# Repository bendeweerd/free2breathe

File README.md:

# free<sub>2</sub>breathe
Calvin University Senior Design Team 17, 2022-2023.

Free<sub>2</sub>breathe is a hazardous gas detector built using [SPEC sensors](https://www.spec-sensors.com/) and a custom PCB. It detects short-term and long-term hazardous levels of
1. Carbon Monoxide
2. Ozone
3. Sulfur Dioxide
4. Nitrogen Dioxide

and alerts the user if any of these gases are present in concentrations that will cause long-term or short-term harm.

Visit our [webpage](https://bendeweerd.github.io/free2breathe/index.html) to download the instructional pamphlet.

Team Members: 
1. Nate Anderson
2. Jordan Alexander
3. Ben DeWeerd
4. Anna Giboney

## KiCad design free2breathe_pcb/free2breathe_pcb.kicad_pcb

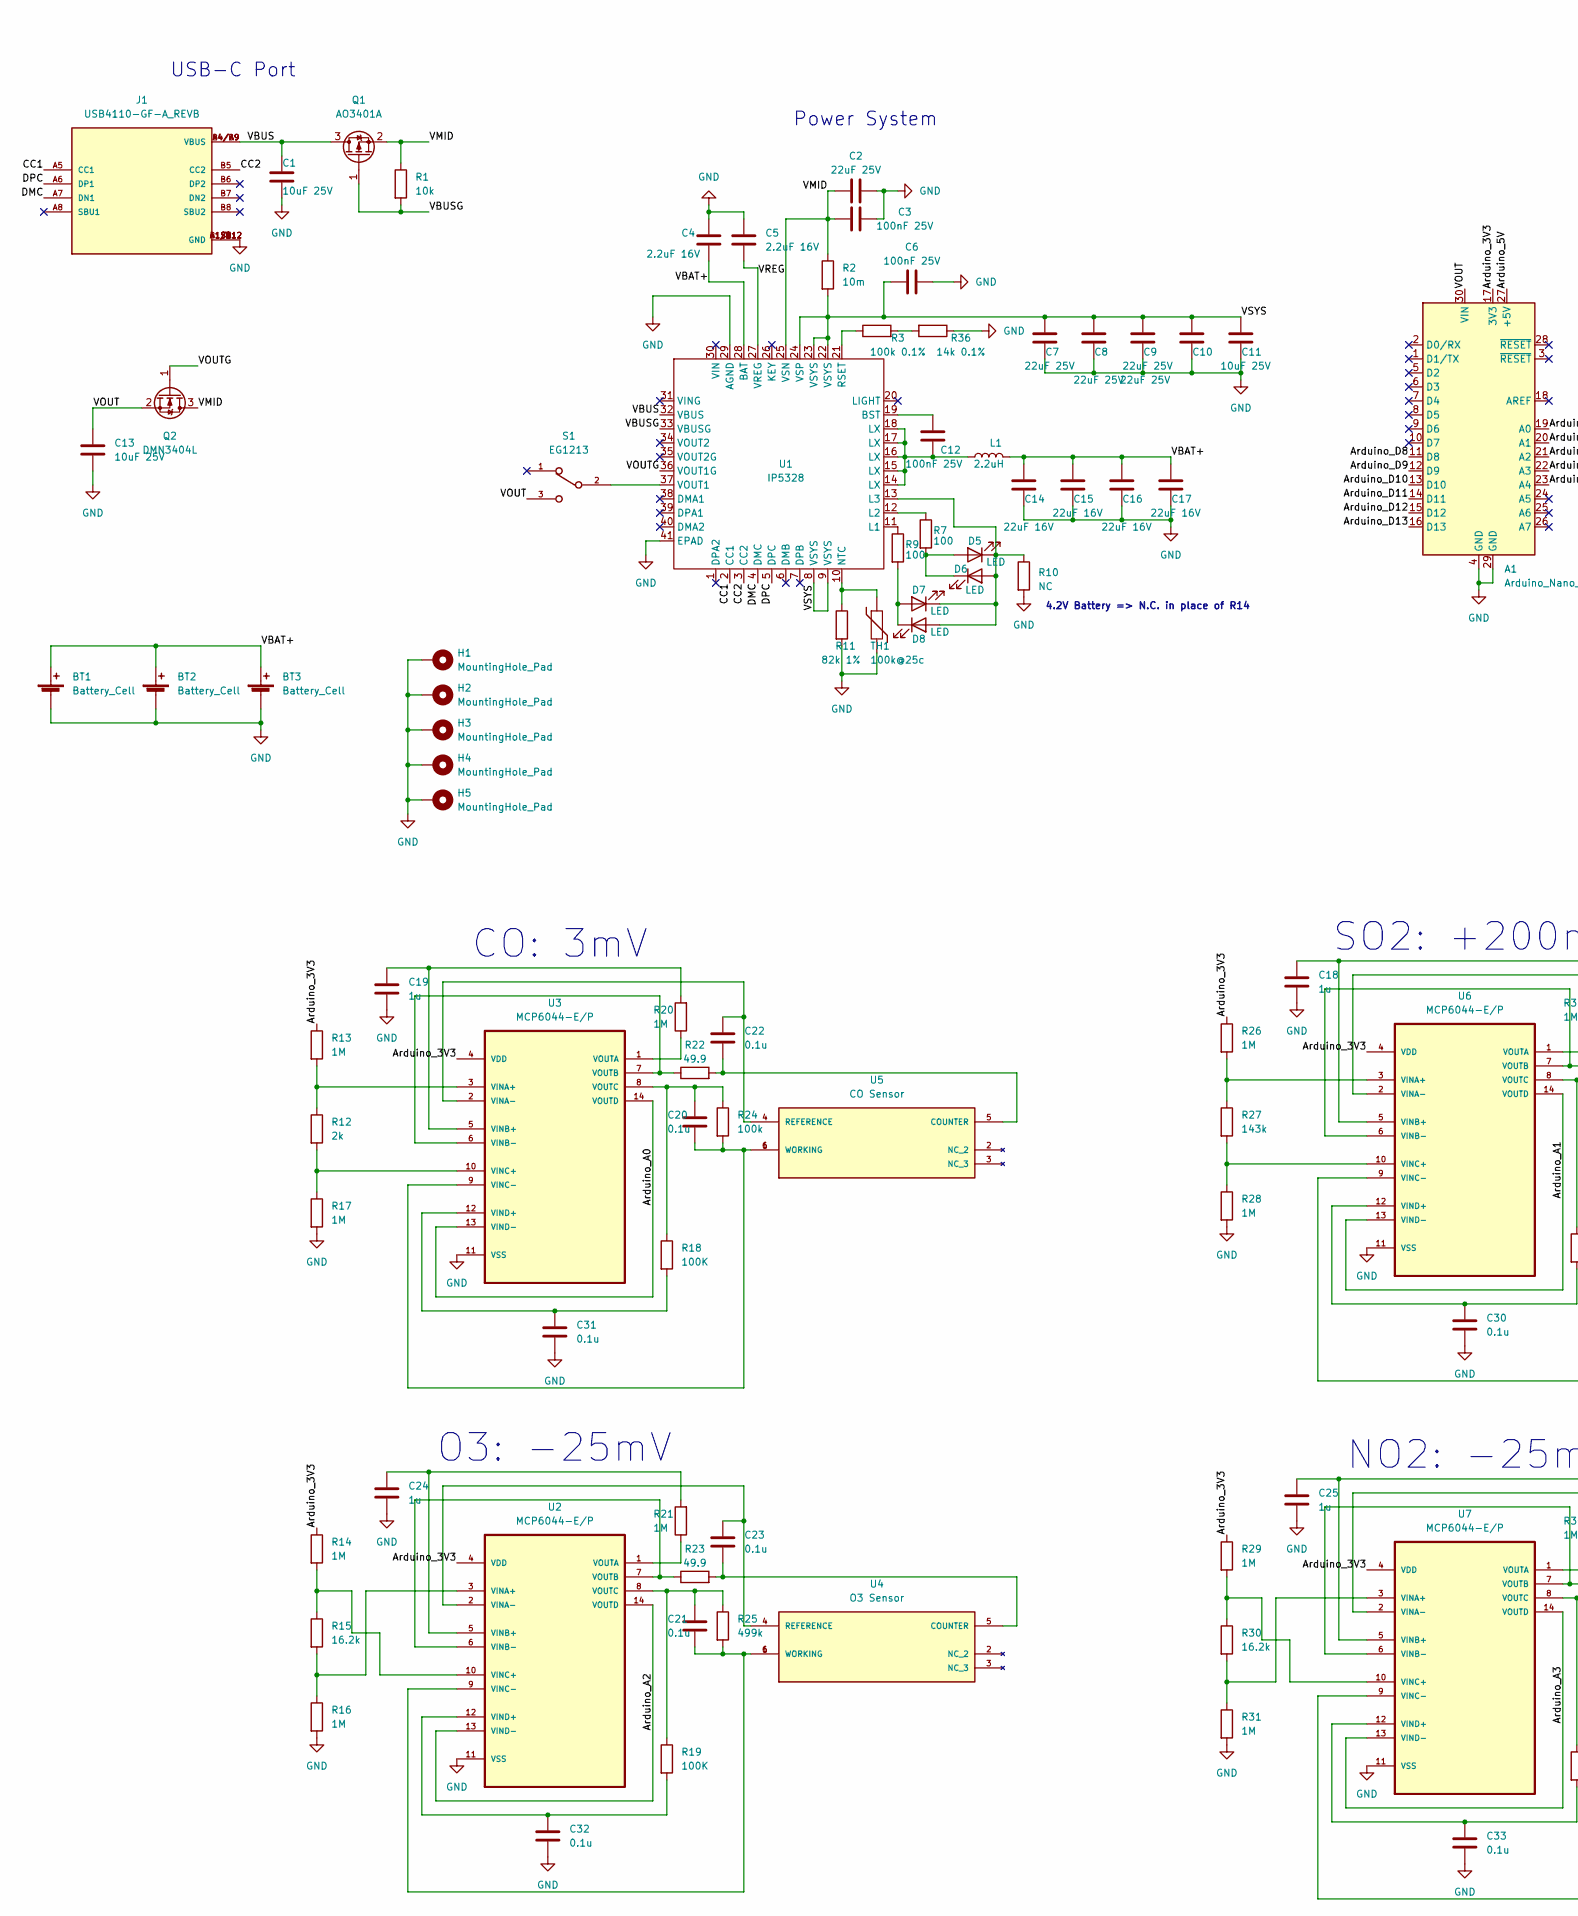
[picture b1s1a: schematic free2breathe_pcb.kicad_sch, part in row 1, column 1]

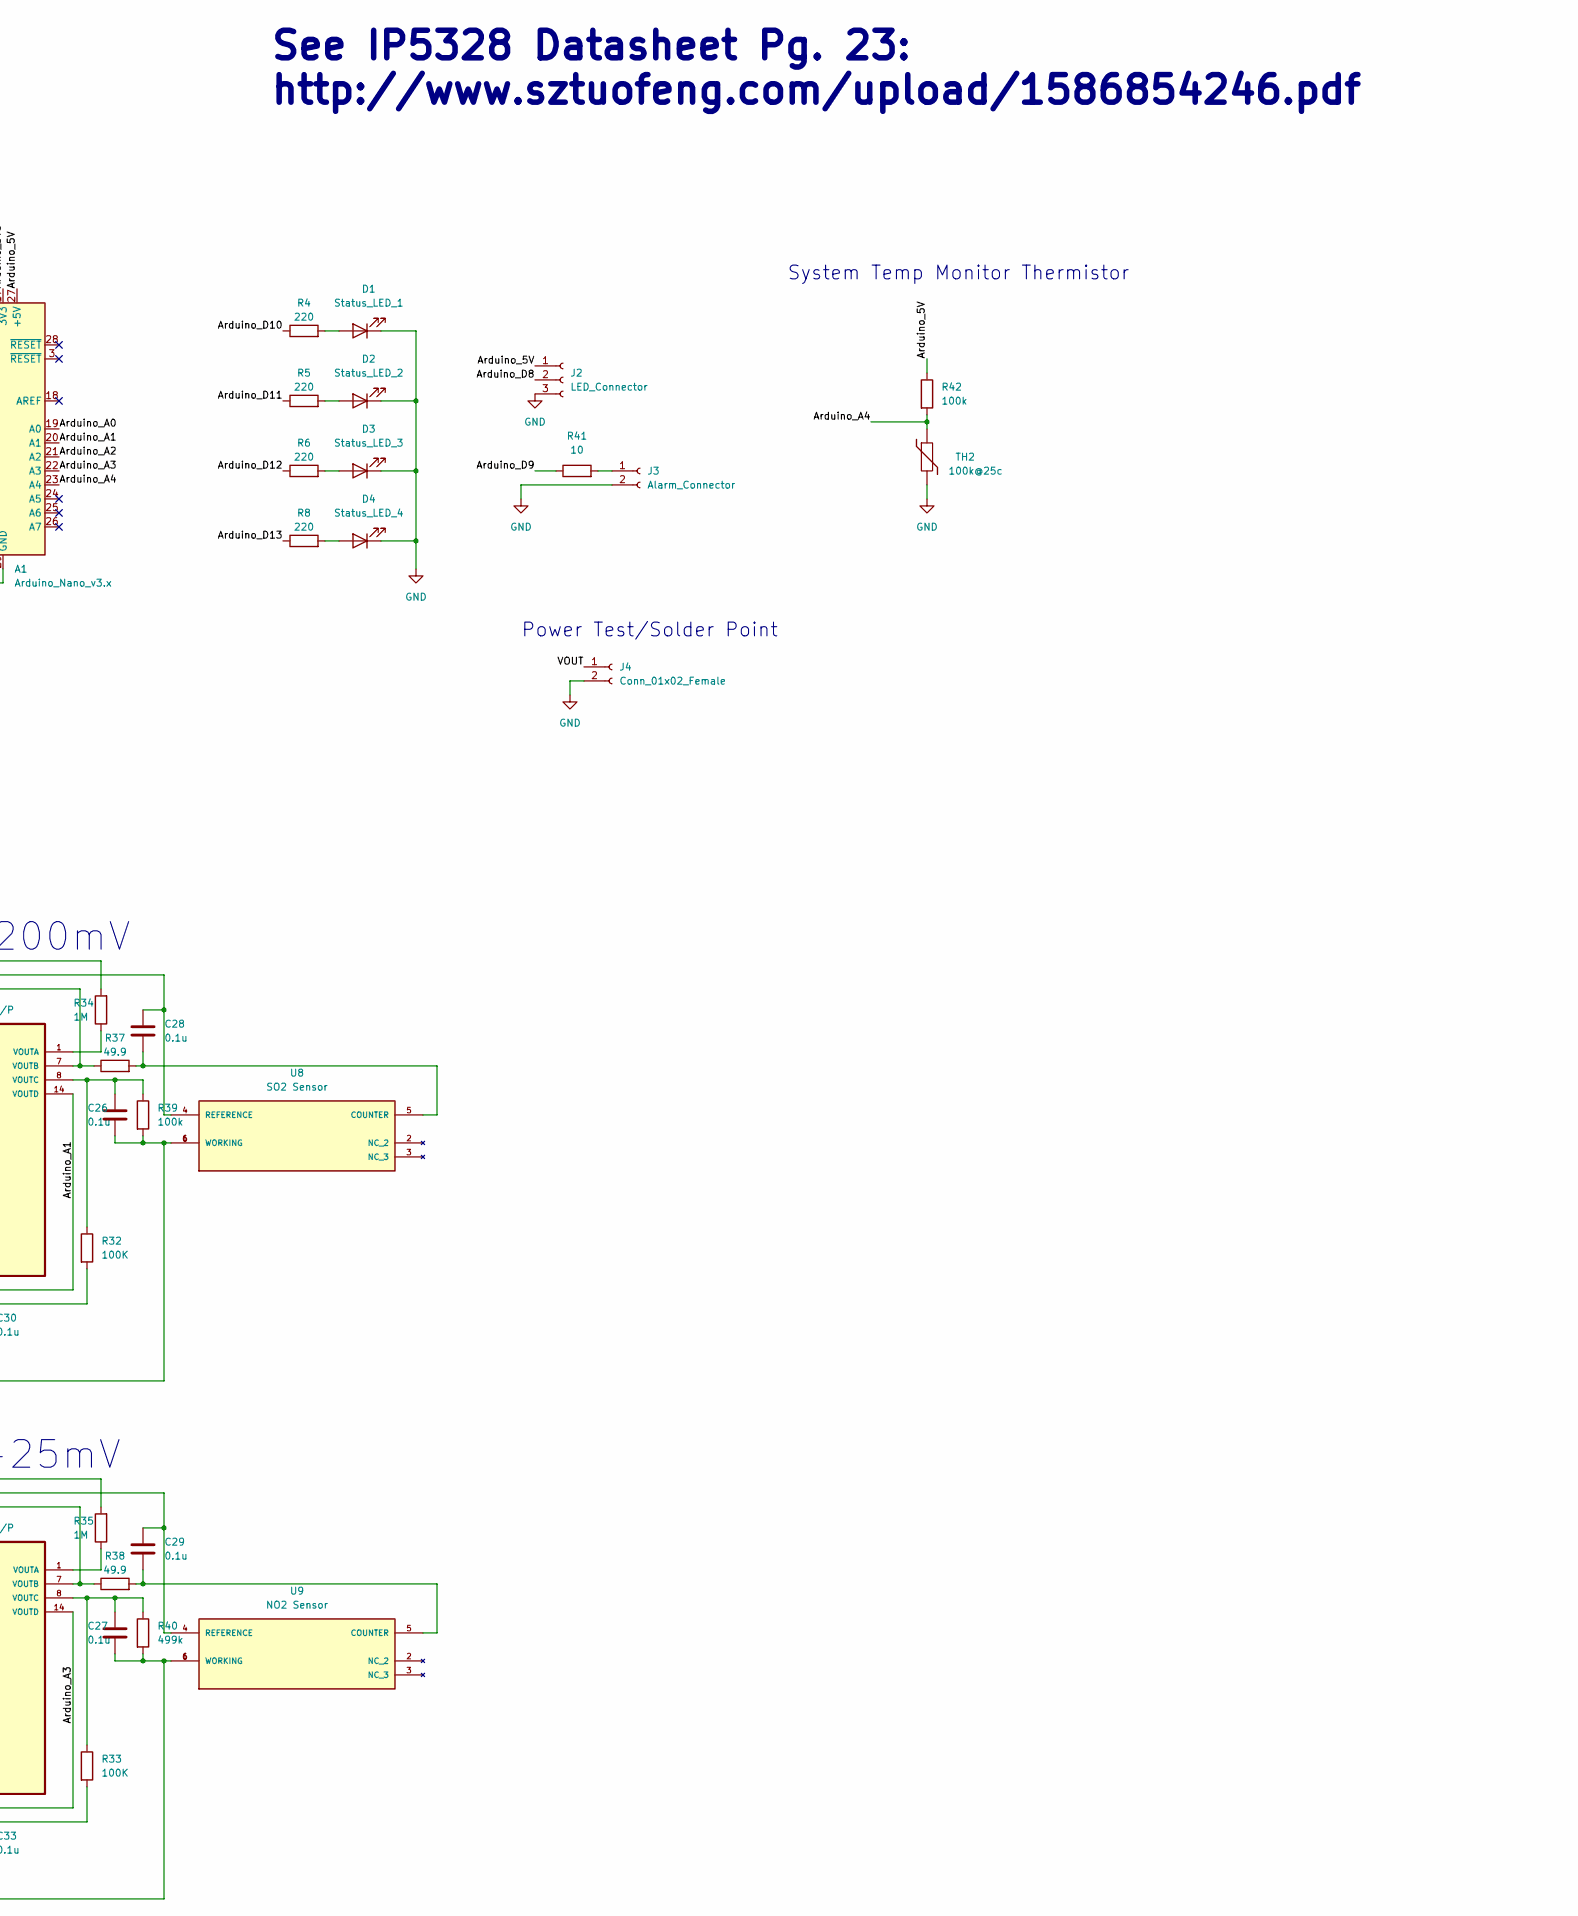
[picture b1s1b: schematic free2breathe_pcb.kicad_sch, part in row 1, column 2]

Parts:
A1: Arduino_Nano_v3.x; Arduino_Nano
BT1, BT2, BT3: Battery_Cell; switch_pad
C1, C11, C13: 10uF 25V; C_0603_1608Metric
C2, C7, C8, C9, C10: 22uF 25V; C_0805_2012Metric
C3, C6, C12: 100nF 25V; C_0603_1608Metric
C4, C5: 2.2uF 16V; C_0603_1608Metric
C14, C15, C16, C17: 22uF 16V; C_0603_1608Metric
C18, C19, C24, C25: 1u; C_0603_1608Metric
C20, C21, C22, C23, C26, C27, C28, C29, C30, C31, C32, C33: 0.1u; C_0603_1608Metric
D1: Status_LED_1; LED_D3.0mm
D2: Status_LED_2; LED_D3.0mm
D3: Status_LED_3; LED_D3.0mm
D4: Status_LED_4; LED_D3.0mm
D5, D6, D7, D8: LED; LED_0603_1608Metric
H1, H2, H3, H4, H5: MountingHole_Pad; MountingHole_3.2mm_M3_Pad_Via
J1: USB4110-GF-A_REVB; GCT_USB4110-GF-A_REVB; PARTREV B
J2: LED_Connector; JST_PH_S3B-PH-K_1x03_P2.00mm_Horizontal
J3: Alarm_Connector; AT_1127_ST_2_R_Alarm
J4: Conn_01x02_Female; switch_pad
L1: 2.2uH; IND_AMPLA5030S2R2MT
Q1: AO3401A; SOT-23
Q2: DMN3404L; SOT-23
R1: 10k; R_0603_1608Metric
R2: 10m; R_0805_2012Metric
R3: 100k 0.1%; R_0603_1608Metric
R4, R5, R6, R8: 220; R_0603_1608Metric
R7, R9: 100; R_0603_1608Metric
R10: NC; R_0603_1608Metric
R11: 82k 1%; R_0603_1608Metric
R12: 2k; R_0603_1608Metric
R13, R14, R16, R17, R20, R21, R26, R28, R29, R31, R34, R35: 1M; R_0603_1608Metric
R15, R30: 16.2k; R_0603_1608Metric
R18, R19, R32, R33: 100K; R_0603_1608Metric
R22, R23, R37, R38: 49.9; R_0603_1608Metric
R24, R39, R42: 100k; R_0603_1608Metric
R25, R40: 499k; R_0603_1608Metric
R27: 143k; R_0603_1608Metric
R36: 14k 0.1%; R_0603_1608Metric
R41: 10; R_0603_1608Metric
S1: EG1213; SW_EG1213
TH1, TH2: 100k@25c; R_0805_2012Metric
U1: IP5328; QFN-40-1EP_6x6mm_P0.5mm_EP4.6x4.6mm
U2, U3, U6, U7: MCP6044-E/P; DIP254P762X533-14; MPN MCP6044-E/P
U4: O3 Sensor; XDCR_110-102; PARTREV April 2017
U5: CO Sensor; XDCR_110-102; PARTREV April 2017
U8: SO2 Sensor; XDCR_110-102; PARTREV April 2017
U9: NO2 Sensor; XDCR_110-102; PARTREV April 2017

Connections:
/Arduino_3V3: A1.17 (3V3), R13.1, R14.1, R26.1, R29.1, U2.4 (VDD), U3.4 (VDD), U6.4 (VDD), U7.4 (VDD)
/Arduino_5V: A1.27 (+5V), J2.1, R42.1
/Arduino_A0: A1.19 (A0), U3.13 (VIND-), U3.14 (VOUTD)
/Arduino_A1: A1.20 (A1), U6.13 (VIND-), U6.14 (VOUTD)
/Arduino_A2: A1.21 (A2), U2.13 (VIND-), U2.14 (VOUTD)
/Arduino_A3: A1.22 (A3), U7.13 (VIND-), U7.14 (VOUTD)
/Arduino_A4: A1.23 (A4), R42.2, TH2.1
/Arduino_D8: A1.11 (D8), J2.2
/Arduino_D9: A1.12 (D9), R41.1
/Arduino_D10: A1.13 (D10), R4.1
/Arduino_D11: A1.14 (D11), R5.1
/Arduino_D12: A1.15 (D12), R6.1
/Arduino_D13: A1.16 (D13), R8.1
/CC1: J1.A5 (CC1), U1.2 (CC1)
/CC2: J1.B5 (CC2), U1.3 (CC2)
/DMC: J1.A7 (DN1), U1.4 (DMC)
/DPC: J1.A6 (DP1), U1.5 (DPC)
/VBAT+: BT1.1 (+), BT2.1 (+), BT3.1 (+), C4.2, C14.1, C15.1, C16.1, C17.1, L1.2, U1.28 (BAT)
/VBUS: C1.1, J1.A4/B9 (VBUS), J1.B4/A9 (VBUS), Q1.3 (D), U1.32 (VBUS)
/VBUSG: Q1.1 (G), R1.2, U1.33 (VBUSG)
/VMID: C2.2, C3.2, Q1.2 (S), Q2.3 (D), R1.1, R2.1, U1.25 (VSN)
/VOUT: A1.30 (VIN), C13.1, J4.1, Q2.2 (S), S1.3
/VOUTG: Q2.1 (G), U1.36 (VOUT1G)
/VREG: C5.2, U1.27 (VREG)
/VSYS: C6.1, C7.1, C8.1, C9.1, C10.1, C11.1, R2.2, U1.8 (VSYS), U1.9 (VSYS), U1.22 (VSYS), U1.23 (VSYS), U1.24 (VSP)
GND: A1.4 (GND), A1.29 (GND), BT1.2 (-), BT2.2 (-), BT3.2 (-), C1.2, C2.1, C3.1, C4.1, C5.1, C6.2, C7.2, C8.2, C9.2, C10.2, C11.2, C13.2, C14.2, C15.2, C16.2, C17.2, C18.2, C19.2, C24.2, C25.2, C30.2, C31.2, C32.2, C33.2, D1.1 (K), D2.1 (K), D3.1 (K), D4.1 (K), H1.1, H2.1, H3.1, H4.1, H5.1, J1.A1/B12 (GND), J1.B1/A12 (GND), J1.S1 (GND), J1.S2 (GND), J1.S3 (GND), J1.S4 (GND), J2.3, J3.2, J4.2, R10.2, R11.2, R16.2, R17.2, R28.2, R31.2, R36.1, TH1.2, TH2.2, U1.29 (AGND), U1.41 (EPAD), U2.11 (VSS), U3.11 (VSS), U6.11 (VSS), U7.11 (VSS)
unnamed: C12.1, U1.19 (BST)
unnamed: C12.2, L1.1, U1.14 (LX), U1.15 (LX), U1.16 (LX), U1.17 (LX), U1.18 (LX)
unnamed: C18.1, R34.2, U6.5 (VINB+)
unnamed: C19.1, R20.2, U3.5 (VINB+)
unnamed: C20.1, R24.2, U3.9 (VINC-), U5.1 (WORKING), U5.6 (WORKING)
unnamed: C20.2, R18.1, R24.1, U3.8 (VOUTC)
unnamed: C21.1, R25.2, U2.9 (VINC-), U4.1 (WORKING), U4.6 (WORKING)
unnamed: C21.2, R19.1, R25.1, U2.8 (VOUTC)
unnamed: C22.1, U3.2 (VINA-), U5.4 (REFERENCE)
unnamed: C22.2, R22.2, U5.5 (COUNTER)
unnamed: C23.1, U2.2 (VINA-), U4.4 (REFERENCE)
unnamed: C23.2, R23.2, U4.5 (COUNTER)
unnamed: C24.1, R21.2, U2.5 (VINB+)
unnamed: C25.1, R35.2, U7.5 (VINB+)
unnamed: C26.1, R39.2, U6.9 (VINC-), U8.1 (WORKING), U8.6 (WORKING)
unnamed: C26.2, R32.1, R39.1, U6.8 (VOUTC)
unnamed: C27.1, R40.2, U7.9 (VINC-), U9.1 (WORKING), U9.6 (WORKING)
unnamed: C27.2, R33.1, R40.1, U7.8 (VOUTC)
unnamed: C28.1, U6.2 (VINA-), U8.4 (REFERENCE)
unnamed: C28.2, R37.2, U8.5 (COUNTER)
unnamed: C29.1, U7.2 (VINA-), U9.4 (REFERENCE)
unnamed: C29.2, R38.2, U9.5 (COUNTER)
unnamed: C30.1, R32.2, U6.12 (VIND+)
unnamed: C31.1, R18.2, U3.12 (VIND+)
unnamed: C32.1, R19.2, U2.12 (VIND+)
unnamed: C33.1, R33.2, U7.12 (VIND+)
unnamed: D1.2 (A), R4.2
unnamed: D2.2 (A), R5.2
unnamed: D3.2 (A), R6.2
unnamed: D4.2 (A), R8.2
unnamed: D5.1 (K), D6.2 (A), D7.1 (K), D8.2 (A), R10.1, U1.13 (L3)
unnamed: D5.2 (A), D6.1 (K), R7.2
unnamed: D7.2 (A), D8.1 (K), R9.2
unnamed: J3.1, R41.2
unnamed: R3.1, U1.21 (RSET)
unnamed: R3.2, R36.2
unnamed: R7.1, U1.12 (L2)
unnamed: R9.1, U1.11 (L1)
unnamed: R11.1, TH1.1, U1.10 (NTC)
unnamed: R12.1, R13.2, U3.3 (VINA+)
unnamed: R12.2, R17.1, U3.10 (VINC+)
unnamed: R14.2, R15.1, U2.10 (VINC+)
unnamed: R15.2, R16.1, U2.3 (VINA+)
unnamed: R20.1, U3.1 (VOUTA)
unnamed: R21.1, U2.1 (VOUTA)
unnamed: R22.1, U3.6 (VINB-), U3.7 (VOUTB)
unnamed: R23.1, U2.6 (VINB-), U2.7 (VOUTB)
unnamed: R26.2, R27.1, U6.3 (VINA+)
unnamed: R27.2, R28.1, U6.10 (VINC+)
unnamed: R29.2, R30.1, U7.10 (VINC+)
unnamed: R30.2, R31.1, U7.3 (VINA+)
unnamed: R34.1, U6.1 (VOUTA)
unnamed: R35.1, U7.1 (VOUTA)
unnamed: R37.1, U6.6 (VINB-), U6.7 (VOUTB)
unnamed: R38.1, U7.6 (VINB-), U7.7 (VOUTB)
unnamed: S1.2, U1.37 (VOUT1)

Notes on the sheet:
NO2: -25mV
O3: -25mV
See IP5328 Datasheet Pg. 23: http://www.sztuofeng.com/upload/1586854246.pdf
USB-C Port
4.2V Battery => N.C. in place of R14
System Temp Monitor Thermistor
Power System
CO: 3mV
Power Test/Solder Point
SO2: +200mV

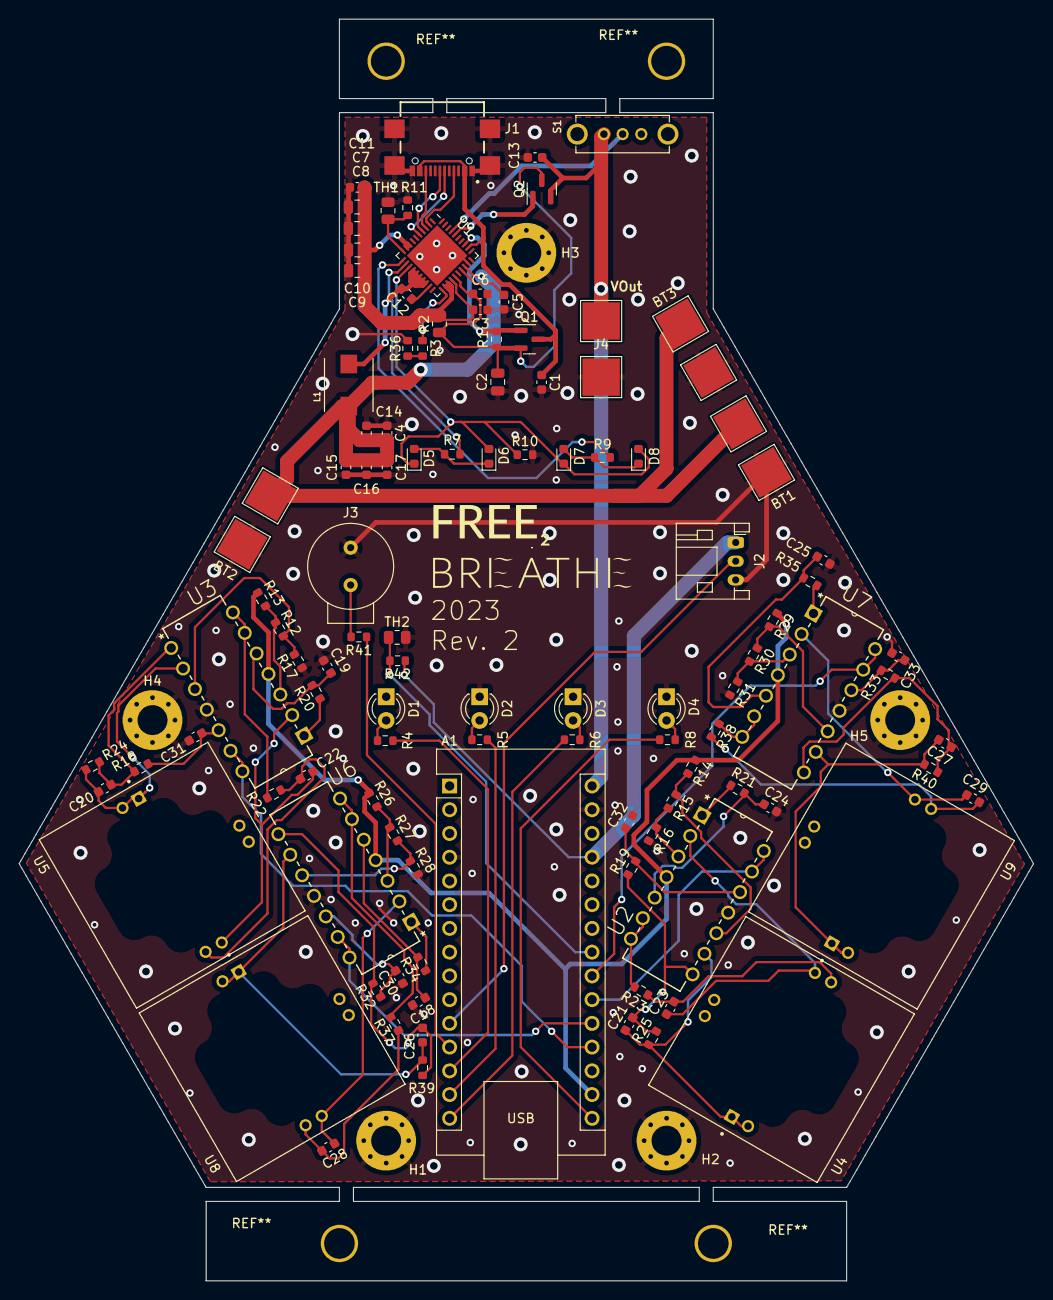
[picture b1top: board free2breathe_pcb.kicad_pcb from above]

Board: 2 copper layers, 108.5 x 135.0 mm, 111 parts (0 on the bottom side), 82 nets.

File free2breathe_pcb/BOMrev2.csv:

Source:,,C:\Users\legen\OneDrive\Documents\SeniorDesign\free2breathe\free2breathe_pcb\free2breathe_pcb.kicad_sch,,,,
Date:,,2/20/2023 15:13,,,,
Tool:,,Eeschema (6.0.9),,,,
Generator:,,C:\Program Files\KiCad\6.0\bin\scripting\plugins/bom_csv_grouped_by_value_with_fp.py,,,,
Component Count:,,111,,,,
Ref,Qnty to Order,Qnty,Value,Cmp name,Footprint,Description
"A1, ",,1,Arduino_Nano_v3.x,Arduino_Nano_v3.x,Module:Arduino_Nano,Arduino Nano v3.x
"BT1, BT2, BT3, ",,3,Battery_Cell,Battery_Cell,switch:switch_pad,Single-cell battery
"C1, C11, C13, ",,3,10uF 25V,C,Capacitor_SMD:C_0603_1608Metric,Unpolarized capacitor
"C2, C7, C8, C9, C10, ",,5,22uF 25V,C,Capacitor_SMD:C_0805_2012Metric,Unpolarized capacitor
"C3, C6, C12, ",6,3,100nF 25V,C,Capacitor_SMD:C_0603_1608Metric,Unpolarized capacitor
"C4, C5, ",,2,2.2uF 16V,C,Capacitor_SMD:C_0603_1608Metric,Unpolarized capacitor
"C14, C15, C16, C17, ",,4,22uF 16V,C,Capacitor_SMD:C_0603_1608Metric,Unpolarized capacitor
"C18, C19, C24, C25, ",8,4,1u,C,Capacitor_SMD:C_0603_1608Metric,Unpolarized capacitor
"C20, C21, C22, C23, C26, C27, C28, C29, C30, C31, C32, C33, ",20,12,0.1u,C,Capacitor_SMD:C_0603_1608Metric,Unpolarized capacitor
"D1, ",,1,Status_LED_1,LED,LED_THT:LED_D3.0mm,Light emitting diode
"D2, ",,1,Status_LED_2,LED,LED_THT:LED_D3.0mm,Light emitting diode
"D3, ",,1,Status_LED_3,LED,LED_THT:LED_D3.0mm,Light emitting diode
"D4, ",,1,Status_LED_4,LED,LED_THT:LED_D3.0mm,Light emitting diode
"D5, D6, D7, D8, ",,4,LED,LED,LED_SMD:LED_0603_1608Metric,Light emitting diode
"H1, H2, H3, H4, H5, ",,5,MountingHole_Pad,MountingHole_Pad,MountingHole:MountingHole_3.2mm_M3_Pad_Via,Mounting Hole with connection
"J1, ",2,1,USB4110-GF-A_REVB,USB4110-GF-A_REVB,components:GCT_USB4110-GF-A_REVB,
"J2, ",,1,LED_Connector,Conn_01x03_Female,Connector_JST:JST_PH_S3B-PH-K_1x03_P2.00mm_Horizontal,"Generic connector, single row, 01x03, script generated (kicad-library-utils/schlib/autogen/connector/)"
"J3, ",,1,Alarm_Connector,Conn_01x02_Female,alarm:AT_1127_ST_2_R_Alarm,"Generic connector, single row, 01x02, script generated (kicad-library-utils/schlib/autogen/connector/)"
"J4, ",,1,Conn_01x02_Female,Conn_01x02_Female,switch:switch_pad,"Generic connector, single row, 01x02, script generated (kicad-library-utils/schlib/autogen/connector/)"
"L1, ",,1,2.2uH,L,components:IND_AMPLA5030S2R2MT,Inductor
"Q1, ",,1,AO3401A,AO3401A,Package_TO_SOT_SMD:SOT-23,"-4.0A Id, -30V Vds, P-Channel MOSFET, SOT-23"
"Q2, ",,1,DMN3404L,DMN3404L,Package_TO_SOT_SMD:SOT-23,"5.8A Id, 30V Vds, N-Channel MOSFET, SOT-23"
"R1, ",,1,10k,R,Resistor_SMD:R_0603_1608Metric,Resistor
"R2, ",,1,10m,R,Resistor_SMD:R_0805_2012Metric,Resistor
"R3, ",,1,100k 0.1%,R,Resistor_SMD:R_0603_1608Metric,Resistor
"R4, R5, R6, R8, ",,4,220,R,Resistor_SMD:R_0603_1608Metric,Resistor
"R7, R9, ",,2,100,R,Resistor_SMD:R_0603_1608Metric,Resistor
"R10, ",,1,NC,R,Resistor_SMD:R_0603_1608Metric,Resistor
"R11, ",,1,82k 1%,R,Resistor_SMD:R_0603_1608Metric,Resistor
"R12, ",2,1,2k,R,Resistor_SMD:R_0603_1608Metric,Resistor
"R13, R14, R16, R17, R20, R21, R26, R28, R29, R31, R34, R35, ",24,12,1M,R,Resistor_SMD:R_0603_1608Metric,Resistor
"R15, R30, ",4,2,16.2k,R,Resistor_SMD:R_0603_1608Metric,Resistor
"R18, R19, R32, R33, R24, R39, R42, ",14,7,100K,R,Resistor_SMD:R_0603_1608Metric,Resistor
"R22, R23, R37, R38, ",8,4,49.9,R,Resistor_SMD:R_0603_1608Metric,Resistor
"R25, R40, ",4,2,499k,R,Resistor_SMD:R_0603_1608Metric,Resistor
"R27, ",2,1,143k,R,Resistor_SMD:R_0603_1608Metric,Resistor
"R36, ",,1,14k 0.1%,R,Resistor_SMD:R_0603_1608Metric,Resistor
"R41, ",,1,10,R,Resistor_SMD:R_0603_1608Metric,Resistor
"S1, ",2,1,EG1213,EG1213,components:SW_EG1213,
"TH1, TH2, ",2,2,100k@25c,Thermistor,Resistor_SMD:R_0805_2012Metric,Temperature dependent resistor
"U1, ",,1,IP5328,IP5328,Package_DFN_QFN:QFN-40-1EP_6x6mm_P0.5mm_EP4.6x4.6mm,
"U2, U3, U6, U7, ",,4,MCP6044-E/P,MCP6044-E/P,components:DIP254P762X533-14,
"U4, ",,1,O3 Sensor,110-102,components:XDCR_110-102,
"U5, ",,1,CO Sensor,110-102,components:XDCR_110-102,
"U8, ",,1,SO2 Sensor,110-102,components:XDCR_110-102,
"U9, ",,1,NO2 Sensor,110-102,components:XDCR_110-102,
,,,,,,

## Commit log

2022-10-17 add basic sensor test code, platformio project, component list
2022-10-17 update file structure to work with platformio
2022-10-17 add kicad project, update gitignore to remove kicad temp files
2022-10-17 remove redundant folder
2022-11-11 start adding pcb components, update gitignore
2022-11-11 undo unecessary gitignore changes
2022-11-19 add LED controller
2022-11-21 add led pulse effect, verify LED functionality
2022-11-22 fix LED color order, add loading effect
2022-11-22 update README, add USB-C connector to schematic
2022-12-02 add CO test file
2022-12-02 update CO sensor reading sketch
2022-12-02 incorporate CO sensor code
2022-12-05 clean up main routine, increase polls
2022-12-06 add warning state, remove unnecessary changeState method
2023-01-10 add additional components, symbols and footprints
2023-01-11 add status LEDs and connectors
2023-01-16 add basic code for additional sensors
2023-01-16 added switch to schematic
2023-01-17 add sensor biasing, assign footprints
2023-01-18 additional footprints, update todo
2023-01-20 add voltage reader
2023-01-20 Sensor code (#1)
    * add basic code for additional sensors
    * add voltage reader
2023-01-23 completed rev1 board schematic
2023-01-23 begun sorting components on layout
2023-01-23 add Ben's stuff
2023-01-23 group sensors with supporting hardware
2023-01-23 begin board layout
2023-01-23 rest of components placed in board (very poorly)
2023-01-23 add new PCB shape, move todo out of /src
2023-01-23 initial arrangement for new layout, add mounting holes
2023-01-24 further refinement
2023-01-24 placed components, changed power LEDs
2023-01-24 some routing done around the bottom sensors
2023-01-24 more routing
2023-01-24 add 3d models
2023-01-24 update step file to include standard components
2023-01-24 update components and todo, swap current-sense resistor to 0805
2023-01-25 further routing, ground planes and sticthing vias
2023-01-25 update todo
2023-01-26 add BOM, update board with component replacements
2023-01-27 moved silkscreen
2023-01-27 add fabrication files, update todo
2023-01-31 update step file, remove non-ready sensor code
2023-01-31 add ulp source files
2023-02-02 update with circuit parameters
2023-02-03 changed schematic to new sensor cirucit
2023-02-03 update components list and todo
2023-02-06 start layout v2
2023-02-06 changed LED resistors, placed rev2 components
2023-02-07 completed rev2
2023-02-07 checked for drc compliance
2023-02-07 framework for additional sensors
2023-02-07 add temperature monitoring
2023-02-07 add buzzer and led control
2023-02-08 edit todo
2023-02-11 Ulp (#2)
    * add ulp source files
    * update with circuit parameters
    * framework for additional sensors
    * add temperature monitoring
    * add buzzer and led control
2023-02-13 update board, todo, components
2023-02-14 update for testing, remove old sensor code
2023-02-20 added BOMrev2
2023-02-24 compile shopping list, update BOM
2023-03-06 add PCB stencil features
2023-03-06 add stencil jig
2023-03-06 add boilerplate webpage
2023-03-06 move and rename main webpage
2023-03-10 update HTML link, lock alignment holes
2023-03-10 actually add updates
2023-03-10 update hole spacing on stencil jig
2023-03-10 adjust stencil jig hole depth
2023-03-17 update BOM after assembly
2023-03-24 update schematic for proper x-istor placement, software for testing rev. 2
2023-03-27 clean up main routine, fix webpage resource link
2023-03-27 add branch updates
2023-04-03 prettify webpage
2023-04-04 corrected transistor layout
2023-04-04 add reading for all sensors, cleanup and README update
2023-04-04 Code cleanup (#3)
    * clean up main routine, fix webpage resource link
    * add branch updates
    * prettify webpage
    * add reading for all sensors, cleanup and README update
